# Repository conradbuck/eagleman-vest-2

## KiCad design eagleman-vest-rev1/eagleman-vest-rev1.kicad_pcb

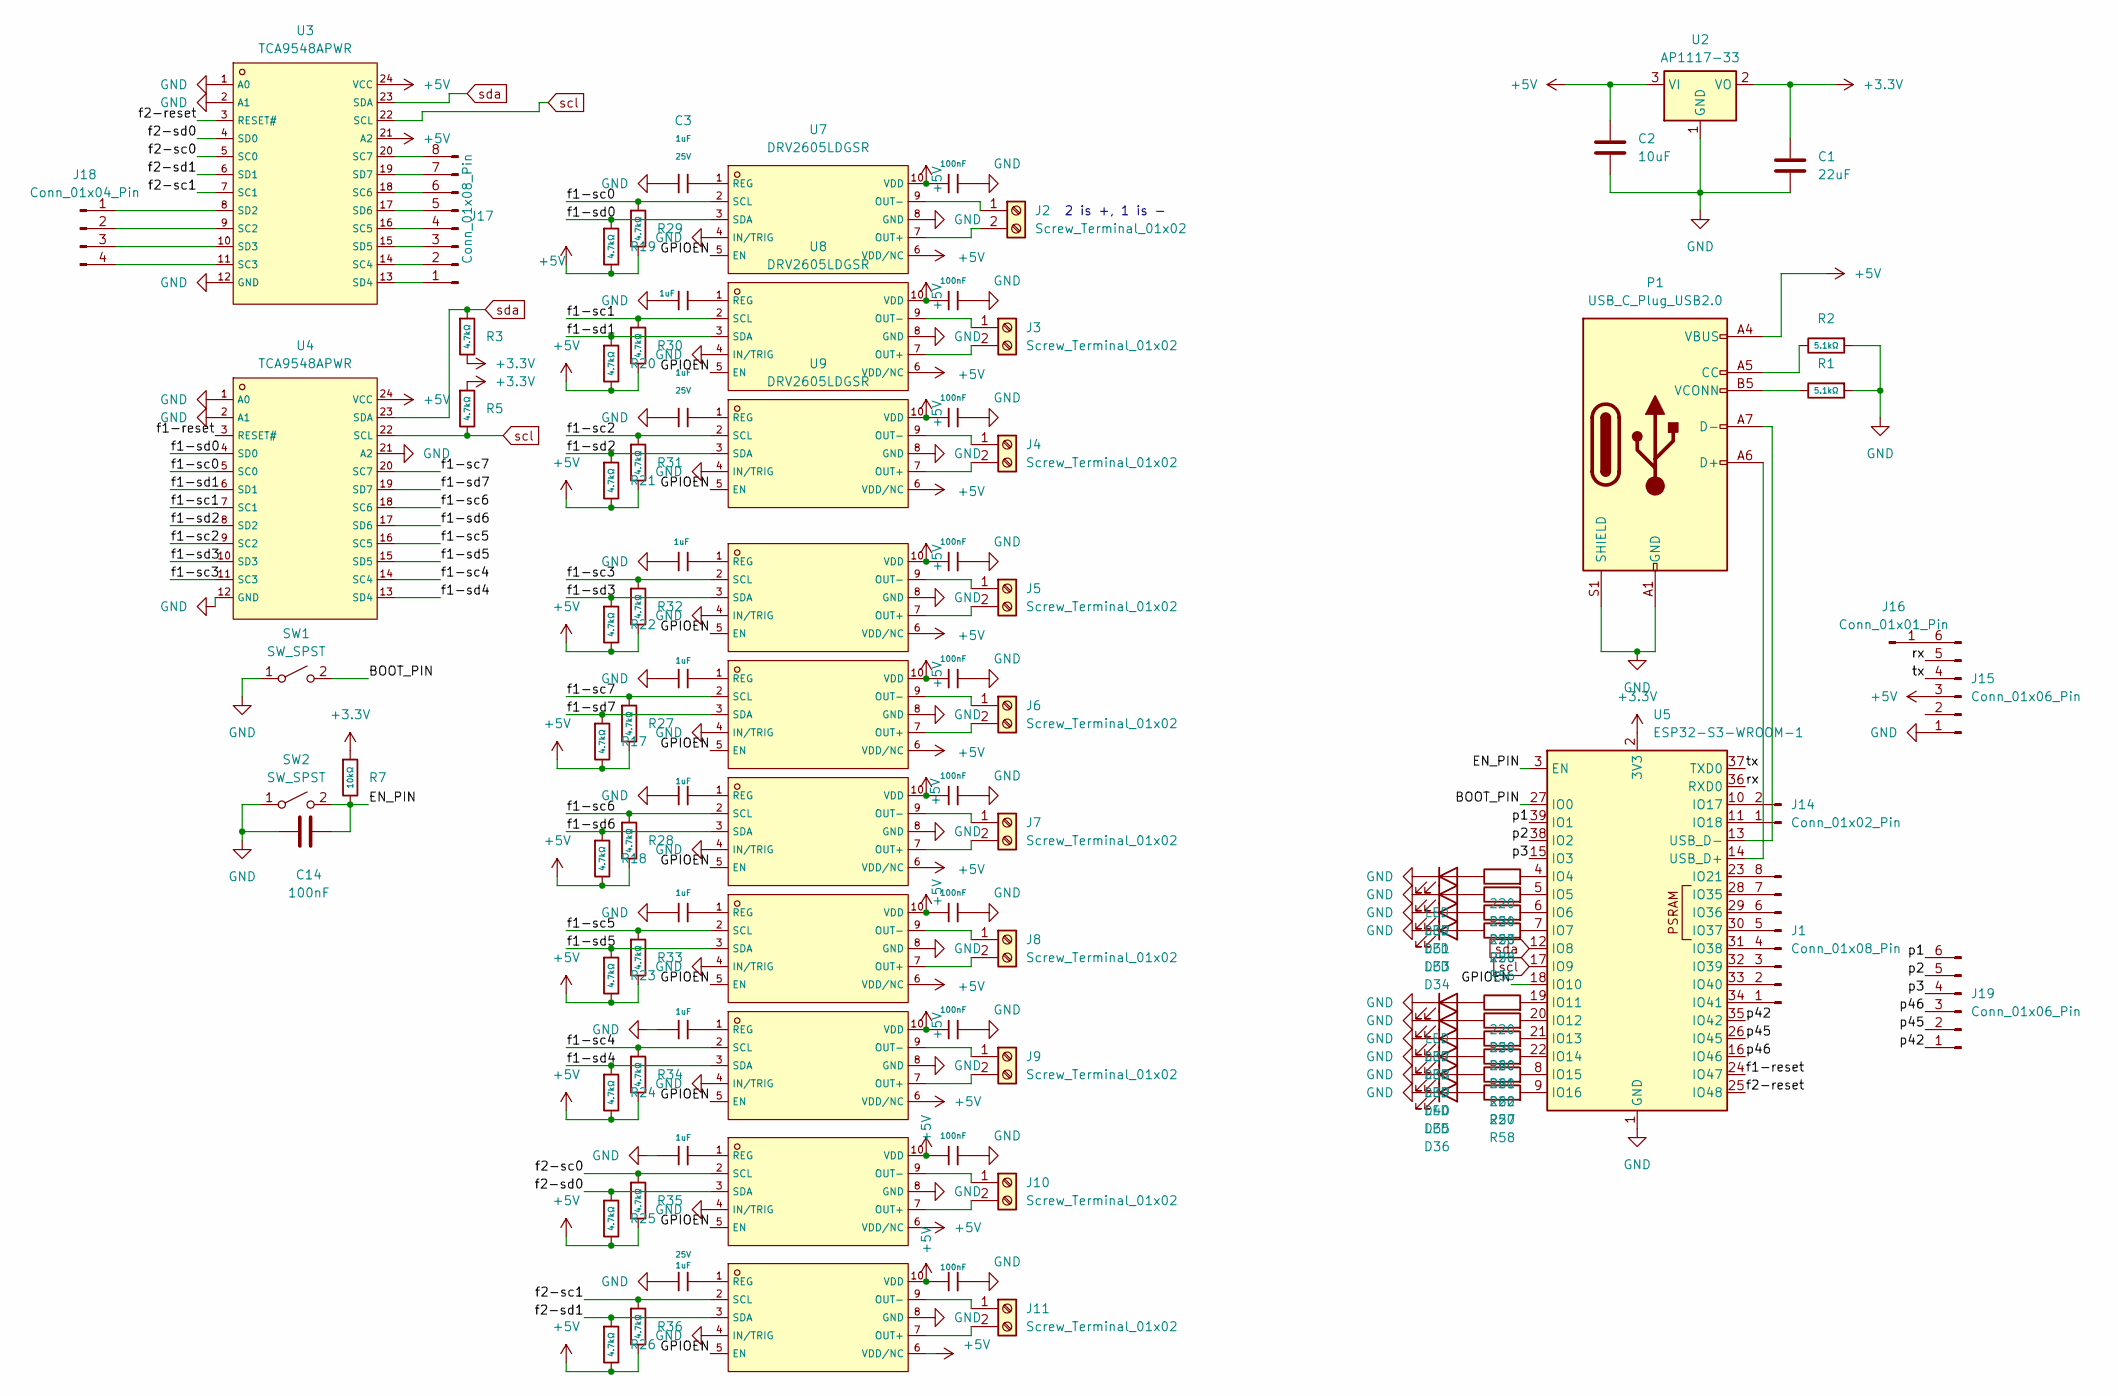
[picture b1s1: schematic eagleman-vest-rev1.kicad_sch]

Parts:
C1: 22uF; C_0805_2012Metric
C2: 10uF; C_0805_2012Metric
C3, C4, C5, C6, C7, C8, C9, C10, C11, C12: 1uF; C_0603_1608Metric; Voltage Rated 25V; Tolerance ±10%; Part CL05A105KA5NQNC; LCSC C52923
C13, C24, C25, C27, C29, C30, C32, C33, C35, C36: 100nF; C_0603_1608Metric; Voltage Rated 16V; Tolerance ±10%; Part CL05B104KO5NNNC; LCSC C1525
C14: 100nF; C_0603_1608Metric
D31, D32, D33, D34, D35, D36, D37, D38, D39, D40: LED; C_0603_1608Metric
J1: Conn_01x08_Pin; PinHeader_1x08_P2.54mm_Vertical
J2, J3, J4, J5, J6, J7, J8, J9, J10, J11: Screw_Terminal_01x02; PhoenixContact_MCV_1,5_2-G-5.08_1x02_P5.08mm_Vertical
J14: Conn_01x02_Pin; PinHeader_1x02_P2.54mm_Vertical
J15, J19: Conn_01x06_Pin; PinHeader_1x06_P2.54mm_Vertical
J16: Conn_01x01_Pin; PinHeader_1x01_P1.27mm_Vertical
J17: Conn_01x08_Pin; PinHeader_1x08_P1.27mm_Vertical
J18: Conn_01x04_Pin; PinHeader_1x04_P1.27mm_Vertical
P1: USB_C_Plug_USB2.0; USB_C_Receptacle_G-Switch_GT-USB-7010ASV
R1, R2: 5.1kΩ; C_0603_1608Metric; Overload Voltage (Max) 150V; Tolerance ±1%; Part 0805W8F5101T5E; LCSC C27834
R3, R5, R17, R18, R19, R20, R21, R22, R23, R24, R25, R26, R27, R28, R29, R30, R31, R32, R33, R34, R35, R36: 4.7kΩ; C_0603_1608Metric; Overload Voltage (Max) 50V; Tolerance ±1%; Part 0402WGF4701TCE; LCSC C25900
R7: 10kΩ; C_0603_1608Metric; Overload Voltage (Max) 50V; Tolerance ±1%; Part 0402WGF1002TCE; LCSC C25744
R53, R54, R55, R56, R57, R58, R59, R60, R61, R62: 220; C_0603_1608Metric
SW1, SW2: SW_SPST; SW_SPST_FSMSM
U2: AP1117-33; SOT-223-3_TabPin2
U3, U4: TCA9548APWR; TSSOP-24_L7.8-W4.4-P0.65-LS6.4-BL; LCSC C130026
U5: ESP32-S3-WROOM-1
U7, U8, U9, U10, U11, U12, U13, U15, U16: DRV2605LDGSR; driver_footprint_maybe; LCSC C527464
U14: DRV2605LDGSR; SOP50P490X110-10N; LCSC C527464

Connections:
+3.3V: C1.1, R3.2, R5.1, R7.1, U2.2 (VO), U5.2 (3V3)
+5V: C2.1, C13.2, C24.2, C25.2, C27.2, C29.2, C30.2, C32.2, C33.2, C35.2, C36.2, J15.3, P1.A4 (VBUS), P1.A9 (VBUS), P1.B4 (VBUS), P1.B9 (VBUS), R17.2, R18.2, R19.2, R20.2, R21.2, R22.2, R23.2, R24.2, R25.2, R26.2, R27.2, R28.2, R29.2, R30.2, R31.2, R32.2, R33.2, R34.2, R35.2, R36.2, U2.3 (VI), U3.21 (A2), U3.24 (VCC), U4.24 (VCC), U7.6 (VDD/NC), U7.10 (VDD), U8.6 (VDD/NC), U8.10 (VDD), U9.6 (VDD/NC), U9.10 (VDD), U10.6 (VDD/NC), U10.10 (VDD), U11.6 (VDD/NC), U11.10 (VDD), U12.6 (VDD/NC), U12.10 (VDD), U13.6 (VDD/NC), U13.10 (VDD), U14.6 (VDD/NC), U14.10 (VDD), U15.6 (VDD/NC), U15.10 (VDD), U16.6 (VDD/NC), U16.10 (VDD)
/BOOT_PIN: SW1.2 (B), U5.27 (IO0)
/EN_PIN: C14.1, R7.2, SW2.2 (B), U5.3 (EN)
/GPIOEN: U5.18 (IO10), U7.5 (EN), U8.5 (EN), U9.5 (EN), U10.5 (EN), U11.5 (EN), U12.5 (EN), U13.5 (EN), U14.5 (EN), U15.5 (EN), U16.5 (EN)
/f1-reset: U4.3 (RESET#), U5.24 (IO47)
/f1-sc0: R29.1, U4.5 (SC0), U7.2 (SCL)
/f1-sc1: R30.1, U4.7 (SC1), U8.2 (SCL)
/f1-sc2: R31.1, U4.9 (SC2), U9.2 (SCL)
/f1-sc3: R32.1, U4.11 (SC3), U10.2 (SCL)
/f1-sc4: R34.1, U4.14 (SC4), U14.2 (SCL)
/f1-sc5: R33.1, U4.16 (SC5), U13.2 (SCL)
/f1-sc6: R28.1, U4.18 (SC6), U12.2 (SCL)
/f1-sc7: R27.1, U4.20 (SC7), U11.2 (SCL)
/f1-sd0: R19.1, U4.4 (SD0), U7.3 (SDA)
/f1-sd1: R20.1, U4.6 (SD1), U8.3 (SDA)
/f1-sd2: R21.1, U4.8 (SD2), U9.3 (SDA)
/f1-sd3: R22.1, U4.10 (SD3), U10.3 (SDA)
/f1-sd4: R24.1, U4.13 (SD4), U14.3 (SDA)
/f1-sd5: R23.1, U4.15 (SD5), U13.3 (SDA)
/f1-sd6: R18.1, U4.17 (SD6), U12.3 (SDA)
/f1-sd7: R17.1, U4.19 (SD7), U11.3 (SDA)
/f2-reset: U3.3 (RESET#), U5.25 (IO48)
/f2-sc0: R35.1, U3.5 (SC0), U15.2 (SCL)
/f2-sc1: R36.1, U3.7 (SC1), U16.2 (SCL)
/f2-sd0: R25.1, U3.4 (SD0), U15.3 (SDA)
/f2-sd1: R26.1, U3.6 (SD1), U16.3 (SDA)
/p1: J19.6, U5.39 (IO1)
/p2: J19.5, U5.38 (IO2)
/p3: J19.4, U5.15 (IO3)
/p42: J19.1, U5.35 (IO42)
/p45: J19.2, U5.26 (IO45)
/p46: J19.3, U5.16 (IO46)
/rx: J15.5, U5.36 (RXD0)
/tx: J15.4, U5.37 (TXD0)
GND: C1.2, C2.2, C3.2, C4.2, C5.2, C6.2, C7.2, C8.2, C9.2, C10.2, C11.2, C12.2, C13.1, C14.2, C24.1, C25.1, C27.1, C29.1, C30.1, C32.1, C33.1, C35.1, C36.1, D31.1 (K), D32.1 (K), D33.1 (K), D34.1 (K), D35.1 (K), D36.1 (K), D37.1 (K), D38.1 (K), D39.1 (K), D40.1 (K), J15.1, P1.A1 (GND), P1.A12 (GND), P1.B1 (GND), P1.B12 (GND), P1.S1 (SHIELD), R1.1, R2.1, SW1.1 (A), SW2.1 (A), U2.1 (GND), U3.1 (A0), U3.2 (A1), U3.12 (GND), U4.1 (A0), U4.2 (A1), U4.12 (GND), U4.21 (A2), U5.1 (GND), U5.40 (GND), U5.41 (GND), U7.4 (IN/TRIG), U7.8 (GND), U8.4 (IN/TRIG), U8.8 (GND), U9.4 (IN/TRIG), U9.8 (GND), U10.4 (IN/TRIG), U10.8 (GND), U11.4 (IN/TRIG), U11.8 (GND), U12.4 (IN/TRIG), U12.8 (GND), U13.4 (IN/TRIG), U13.8 (GND), U14.4 (IN/TRIG), U14.8 (GND), U15.4 (IN/TRIG), U15.8 (GND), U16.4 (IN/TRIG), U16.8 (GND)
unnamed: D31.2 (A), R53.1
unnamed: D32.2 (A), R54.1
unnamed: D33.2 (A), R55.1
unnamed: D34.2 (A), R56.1
unnamed: D35.2 (A), R57.1
unnamed: D36.2 (A), R58.1
unnamed: D37.2 (A), R59.1
unnamed: D38.2 (A), R60.1
unnamed: D39.2 (A), R61.1
unnamed: D40.2 (A), R62.1
unnamed: J1.1, U5.34 (IO41)
unnamed: J1.2, U5.33 (IO40)
unnamed: J1.3, U5.32 (IO39)
unnamed: J1.4, U5.31 (IO38)
unnamed: J1.5, U5.30 (IO37)
unnamed: J1.6, U5.29 (IO36)
unnamed: J1.7, U5.28 (IO35)
unnamed: J1.8, U5.23 (IO21)
unnamed: J2.1, U7.9 (OUT-)
unnamed: J2.2, U7.7 (OUT+)
unnamed: J3.1, U8.9 (OUT-)
unnamed: J3.2, U8.7 (OUT+)
unnamed: J4.1, U9.9 (OUT-)
unnamed: J4.2, U9.7 (OUT+)
unnamed: J5.1, U10.9 (OUT-)
unnamed: J5.2, U10.7 (OUT+)
unnamed: J6.1, U11.9 (OUT-)
unnamed: J6.2, U11.7 (OUT+)
unnamed: J7.1, U12.9 (OUT-)
unnamed: J7.2, U12.7 (OUT+)
unnamed: J8.1, U13.9 (OUT-)
unnamed: J8.2, U13.7 (OUT+)
unnamed: J9.1, U14.9 (OUT-)
unnamed: J9.2, U14.7 (OUT+)
unnamed: J10.1, U15.9 (OUT-)
unnamed: J10.2, U15.7 (OUT+)
unnamed: J11.1, U16.9 (OUT-)
unnamed: J11.2, U16.7 (OUT+)
unnamed: J14.1, U5.11 (IO18)
unnamed: J14.2, U5.10 (IO17)
unnamed: J15.6, J16.1
unnamed: J17.1, U3.13 (SD4)
unnamed: J17.2, U3.14 (SC4)
unnamed: J17.3, U3.15 (SD5)
unnamed: J17.4, U3.16 (SC5)
unnamed: J17.5, U3.17 (SD6)
unnamed: J17.6, U3.18 (SC6)
unnamed: J17.7, U3.19 (SD7)
unnamed: J17.8, U3.20 (SC7)
unnamed: J18.1, U3.8 (SD2)
unnamed: J18.2, U3.9 (SC2)
unnamed: J18.3, U3.10 (SD3)
unnamed: J18.4, U3.11 (SC3)
unnamed: P1.A5 (CC), R2.2
unnamed: P1.A6 (D+), U5.14 (USB_D+)
unnamed: P1.A7 (D-), U5.13 (USB_D-)
unnamed: P1.B5 (VCONN), R1.2
unnamed: R54.2, U5.4 (IO4)
unnamed: R53.2, U5.5 (IO5)
unnamed: R55.2, U5.6 (IO6)
unnamed: R56.2, U5.7 (IO7)
unnamed: R59.2, U5.19 (IO11)
unnamed: R60.2, U5.20 (IO12)
unnamed: R61.2, U5.21 (IO13)
unnamed: R62.2, U5.22 (IO14)
unnamed: R57.2, U5.8 (IO15)
unnamed: R58.2, U5.9 (IO16)
unnamed: C3.1, U7.1 (REG)
unnamed: C4.1, U8.1 (REG)
unnamed: C5.1, U9.1 (REG)
unnamed: C6.1, U10.1 (REG)
unnamed: C7.1, U11.1 (REG)
unnamed: C8.1, U12.1 (REG)
unnamed: C9.1, U13.1 (REG)
unnamed: C10.1, U14.1 (REG)
unnamed: C11.1, U15.1 (REG)
unnamed: C12.1, U16.1 (REG)
scl: R5.2, U3.22 (SCL), U4.22 (SCL), U5.17 (IO9)
sda: R3.1, U3.23 (SDA), U4.23 (SDA), U5.12 (IO8)

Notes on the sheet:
2 is +, 1 is -

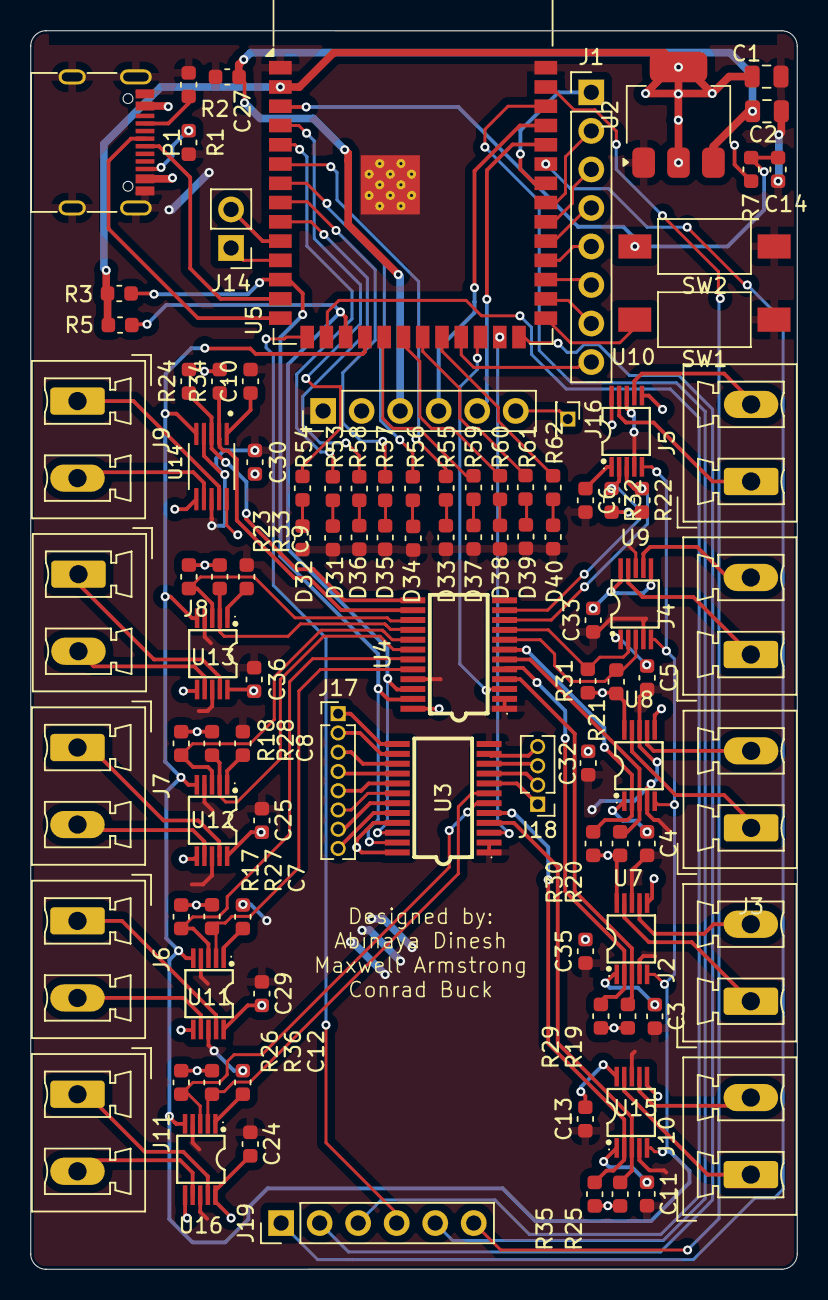
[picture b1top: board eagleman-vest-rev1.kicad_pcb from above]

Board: 2 copper layers, 50.5 x 81.7 mm, 102 parts (0 on the bottom side), 115 nets.

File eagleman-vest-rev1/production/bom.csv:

Designator,Footprint,Quantity,Value,LCSC Part #
C1,0805,1,22uF,
"C10, C11, C12, C3, C4, C5, C6, C7, C8, C9",0603,10,1uF,C52923
"C13, C24, C25, C27, C29, C30, C32, C33, C35, C36",0603,10,100nF,C1525
C14,0603,1,100nF,
C2,0805,1,10uF,
"D31, D32, D33, D34, D35, D36, D37, D38, D39, D40",0603,10,LED,
J1,PinHeader_1x08_P2.54mm_Vertical,1,Conn_01x08_Pin,
"J10, J11, J2, J3, J4, J5, J6, J7, J8, J9","PhoenixContact_MCV_1,5_2-G-5.08_1x02_P5.08mm_Vertical",10,Screw_Terminal_01x02,
J14,PinHeader_1x02_P2.54mm_Vertical,1,Conn_01x02_Pin,
"J15, J19",PinHeader_1x06_P2.54mm_Vertical,2,Conn_01x06_Pin,
J16,PinHeader_1x01_P1.27mm_Vertical,1,Conn_01x01_Pin,
J17,PinHeader_1x08_P1.27mm_Vertical,1,Conn_01x08_Pin,
J18,PinHeader_1x04_P1.27mm_Vertical,1,Conn_01x04_Pin,
P1,USB_C_Receptacle_G-Switch_GT-USB-7010ASV,1,USB_C_Plug_USB2.0,
"R1, R2",0603,2,5.1kΩ,C27834
"R17, R18, R19, R20, R21, R22, R23, R24, R25, R26, R27, R28, R29, R3, R30, R31, R32, R33, R34, R35, R36, R5",0603,22,4.7kΩ,C25900
"R53, R54, R55, R56, R57, R58, R59, R60, R61, R62",0603,10,220,
R7,0603,1,10kΩ,C25744
"SW1, SW2",SW_SPST_FSMSM,2,SW_SPST,
"U10, U11, U12, U13, U15, U16, U7, U8, U9",driver_footprint_maybe,9,DRV2605LDGSR,C527464
U14,SOP50P490X110-10N,1,DRV2605LDGSR,C527464
U2,SOT-223-3_TabPin2,1,AP1117-33,
"U3, U4",TSSOP-24_L7.8-W4.4-P0.65-LS6.4-BL,2,TCA9548APWR,C130026
U5,ESP32-S3-WROOM-1,1,ESP32-S3-WROOM-1,

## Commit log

2025-04-12 added redme
2025-04-12 added kicad file
2025-04-12 added maxwell fules
2025-04-12 add motor driver schematic
2025-04-12 starting to fix wiring w netlabels
2025-04-12 removed duplicate esp32 - why is its footprint not gone?
2025-04-14 started routing
2025-04-14 fixed up, might still be too dense
2025-04-14 more updates
2025-04-15 i need help
2025-04-17 updated routing and lowered density a little bit
2025-04-17 added manufacturing files
2025-04-24 added jlc export zip for reference
2025-04-24 added two firmware samples
2025-04-25 added led functions
2025-04-25 added raw code
2025-04-26 Added a way to disconnect the TCAs without reset, code current working
2025-04-26 added setAllMotor function, tested and functional
2025-04-26 added orchestrator, bluetooth communication
2025-04-26 added motor control
2025-04-26 added continuous robot updating
2025-04-26 here is a file
2025-04-26 final orch
2025-04-26 almost done
    lalala#
2025-04-26 works
2025-04-26 visualizations working
